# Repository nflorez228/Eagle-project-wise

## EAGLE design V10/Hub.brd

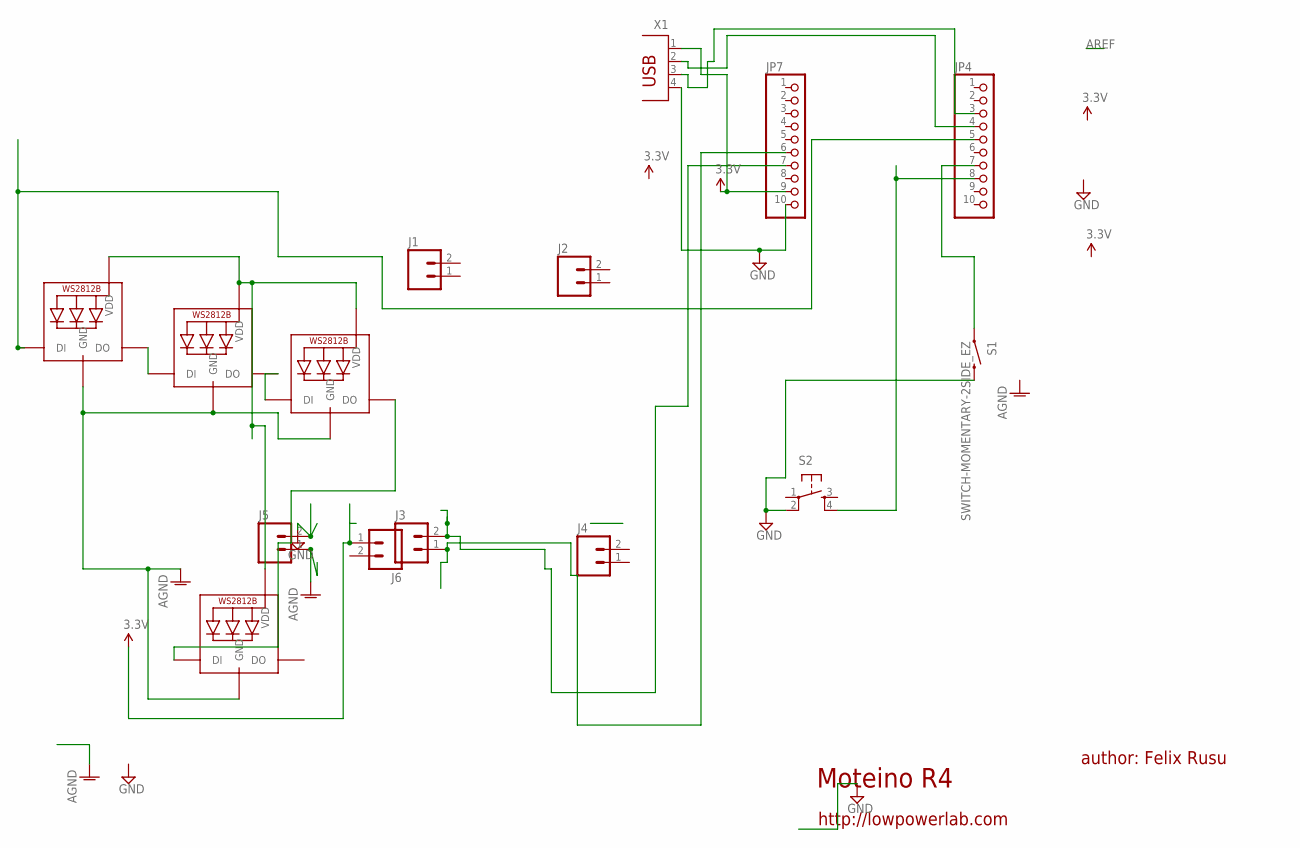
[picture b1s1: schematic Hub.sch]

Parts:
J1, J2, J3, J4, J5, J6: M02PTH; 1X02
JP4, JP7: PINHD-1X10; 1X10
LED1, LED2, LED3, LED5: WS2812B5050; WS2812B
S1: SWITCH-MOMENTARY-2SIDE_EZ; TACTILE-PTH-SIDEEZ
S2: TAC_SWITCHPTH; TACTILE-PTH
X1: PN87520

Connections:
AGND: J5.1, LED1.3-GND (GND), LED2.3-GND (GND), LED3.3-GND (GND), LED5.3-GND (GND)
GND: J5.2, JP7.10, S1.2, S2.2, X1.4
unnamed: JP4.8, S2.4
unnamed: LED3.2-DOUT (DO), LED5.4-DIN (DI)
unnamed: JP4.5, LED1.4-DIN (DI)
unnamed: LED1.1-VDD (VDD), LED2.1-VDD (VDD), LED3.1-VDD (VDD), LED5.1-VDD (VDD)
unnamed: JP4.7, S1.1
unnamed: J3.2, JP7.7
unnamed: J3.1, JP7.6
unnamed: JP4.4, X1.2
unnamed: JP4.3, X1.3
unnamed: LED2.2-DOUT (DO), LED3.4-DIN (DI)
unnamed: LED1.2-DOUT (DO), LED2.4-DIN (DI)
VCC: J6.1, JP7.9, X1.1

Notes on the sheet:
Moteino R4
author: Felix Rusu
http://lowpowerlab.com

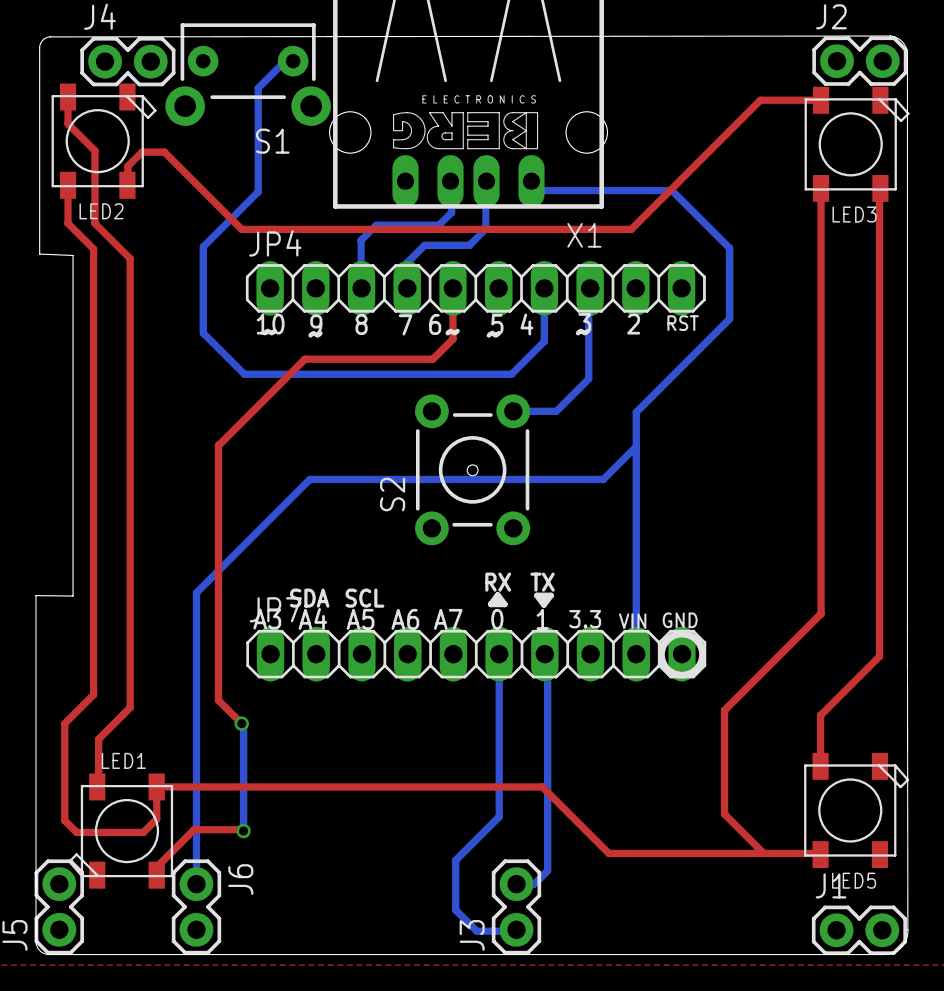
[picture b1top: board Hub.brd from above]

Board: 2 copper layers, 48.4 x 51.0 mm, 15 parts (0 on the bottom side), 14 nets.

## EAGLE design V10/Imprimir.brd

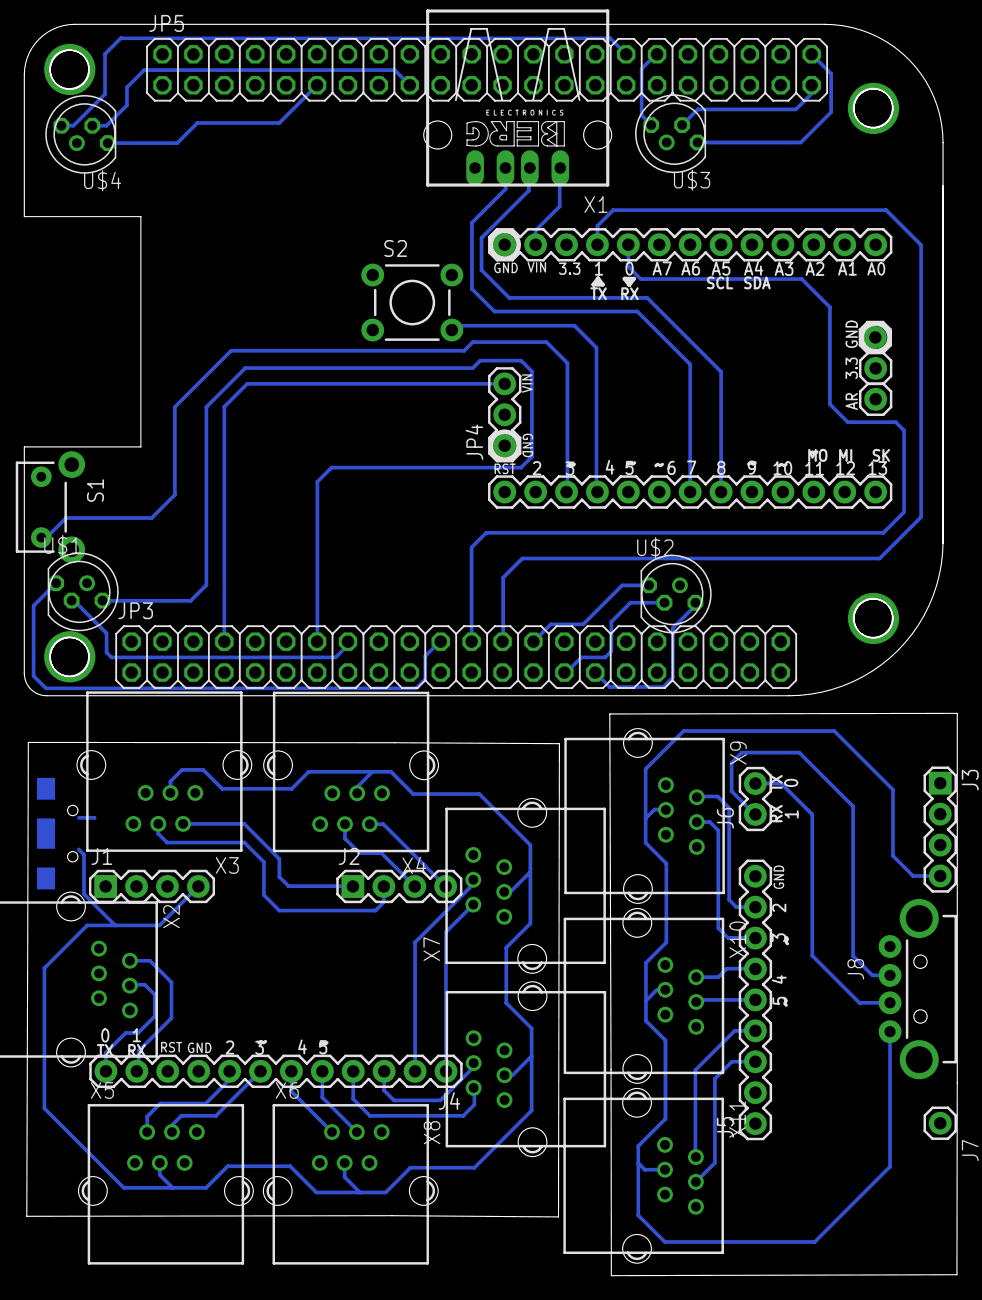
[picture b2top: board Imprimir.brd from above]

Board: 2 copper layers, 76.7 x 102.8 mm, 34 parts (1 on the bottom side), 47 nets.

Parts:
+: M01PTH; 1X01
ANALOGSIDE: M13; 1X13
DIGITALSIDE: M13; 1X13
J1, J2, J3: 1X04
J4: 1X12
J5: 1X09
J6: 1X02
J7: 1X01
J8: USB-A-H
JP1, JP2: M01PTH; 1X01
JP3, JP5: 2X22
JP4: 1X03
JP9: Micro USB; USB-AB-MICRO-SMD_V03
S1: SWITCH-MOMENTARY-2SIDE_EZ; TACTILE-PTH-SIDEEZ
S2: TACTILE-PTH
U$1, U$2, U$3, U$4: 5MMRGBLED; LED5MMRGB
X1: PN87520
X2, X3, X4, X5, X6, X7, X8, X9, X10, X11: YH-55-10

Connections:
GND: ANALOGSIDE.13, JP3.43, JP3.44, S1.1, S2.2, U$1.P$3, U$2.P$3, U$3.P$3, U$4.P$3, X1.4
GND1: J1.2, J4.9, JP9.GND1, X2.5, X3.5, X4.5, X5.5, X6.5, X7.5, X8.5
GND2: J3.2, J5.9, J8.VBUS, X9.5, X10.5, X11.5
unnamed: DIGITALSIDE.10, S2.4
unnamed: ANALOGSIDE.9, JP3.24
unnamed: JP3.14, U$1.P$4
unnamed: J4.12, X2.4
unnamed: JP3.16, U$1.P$2
unnamed: DIGITALSIDE.11, S1.2
unnamed: JP3.22, U$1.P$1
unnamed: JP3.28, U$2.P$1
unnamed: JP3.29, U$2.P$2
unnamed: JP3.31, U$2.P$4
unnamed: JP5.11, U$4.P$1
unnamed: JP5.17, U$4.P$2
unnamed: JP5.32, U$4.P$4
unnamed: JP5.43, U$3.P$2
unnamed: JP5.44, U$3.P$1
unnamed: JP5.34, U$3.P$4
unnamed: ANALOGSIDE.10, JP3.26
unnamed: DIGITALSIDE.7, X1.3
unnamed: ANALOGSIDE.12, X1.1
unnamed: DIGITALSIDE.6, X1.2
unnamed: J4.11, X2.2
unnamed: J4.7, X5.4
unnamed: J4.8, X5.2
unnamed: J4.5, X6.4
unnamed: J4.6, X6.2
unnamed: J4.3, X8.4
unnamed: J4.4, X8.2
unnamed: J4.2, X7.4
unnamed: J4.1, X7.2
unnamed: J2.4, X4.2
unnamed: J2.3, X4.4
unnamed: J2.2, X3.4
unnamed: J2.1, X3.2
unnamed: J5.7, X9.4
unnamed: J5.8, X9.2
unnamed: J5.5, X10.4
unnamed: J5.6, X10.2
unnamed: J5.3, X11.4
unnamed: J5.4, X11.2
unnamed: J6.2, J8.D+
unnamed: J6.1, J8.D-
VCC: JP3.8, JP4.3
VIN: J1.4, JP9.VBUS1, X3.3, X4.3, X5.3, X6.3, X7.3, X8.3
VIN1: J3.4, J8.GND, X9.3, X10.3, X11.3

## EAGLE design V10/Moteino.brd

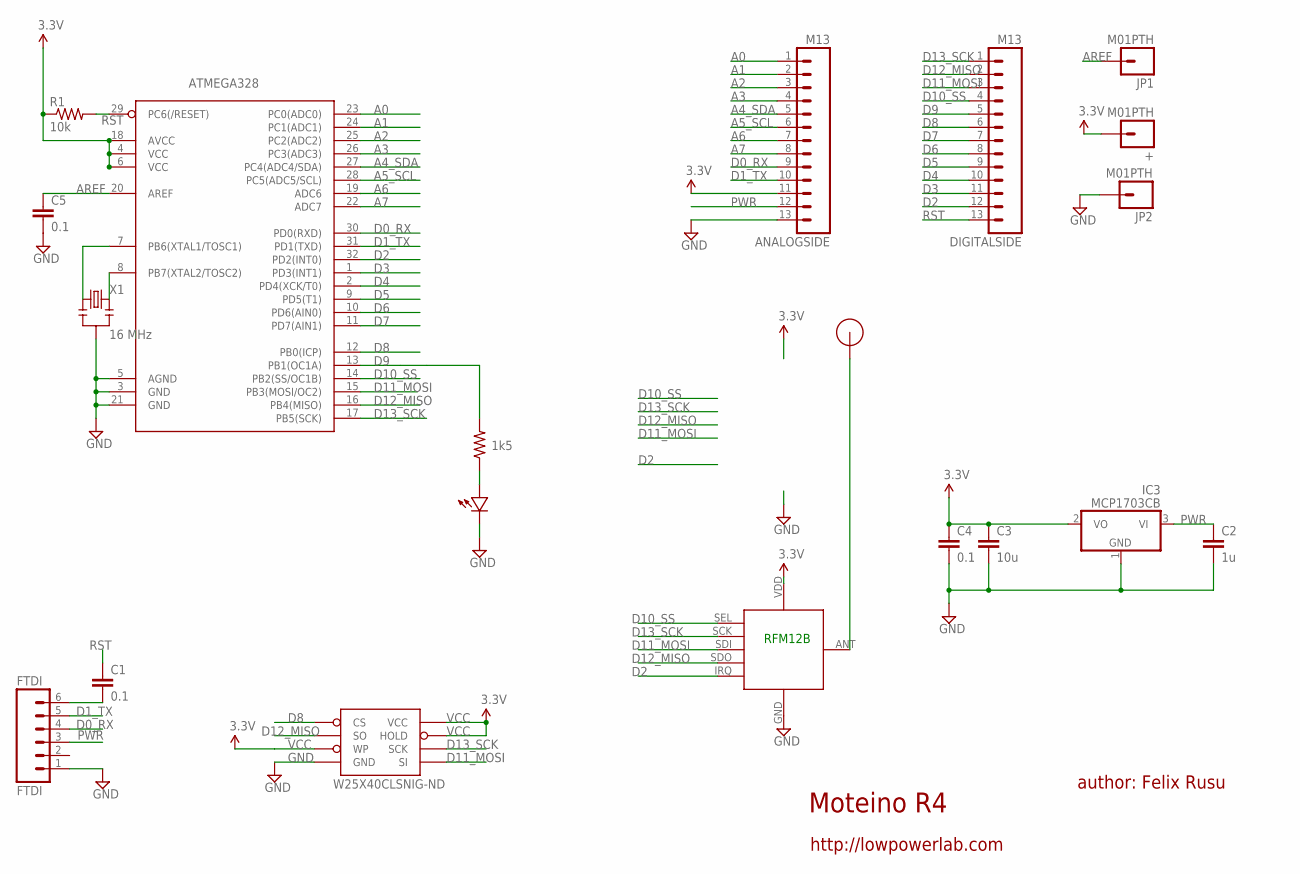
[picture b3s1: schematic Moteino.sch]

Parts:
+: M01PTH; 1X01
ANALOGSIDE: M13; 1X13
ATMEGA328: ATMega-328; TQFP32-08
C1, C4, C5: 0.1; 0603-CAP
C2: 1u; 0603-CAP
C3: 10u; 0805-CAP
DIGITALSIDE: M13; 1X13
FTDI: FTDI; 1X06
IC3: MCP1703CB; SOT23
JP1, JP2: M01PTH; 1X01
R1: 10k; 0603-RES
R2: 1k5; 0603-RES
RFM12B: RFM12B_MINPADS; RFM12B-MINPADS
U$1: RFM12B_ANTENNA; RFM12B-ANTENNA
U$2: LED0603; 0603-LED
W25X40CLSNIG-ND: AT25F512BWIDE_5.3MM; SO08WIDE
X1: 16 MHz; RESONATOR-SMD

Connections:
A0: ANALOGSIDE.1, ATMEGA328.23 (PC0(ADC0))
A1: ANALOGSIDE.2, ATMEGA328.24 (PC1(ADC1))
A2: ANALOGSIDE.3, ATMEGA328.25 (PC2(ADC2))
A3: ANALOGSIDE.4, ATMEGA328.26 (PC3(ADC3))
A4_SDA: ANALOGSIDE.5, ATMEGA328.27 (PC4(ADC4/SDA))
A5_SCL: ANALOGSIDE.6, ATMEGA328.28 (PC5(ADC5/SCL))
A6: ANALOGSIDE.7, ATMEGA328.19 (ADC6)
A7: ANALOGSIDE.8, ATMEGA328.22 (ADC7)
AREF: ATMEGA328.20 (AREF), C5.1, JP1.1
D0_RX: ANALOGSIDE.9, ATMEGA328.30 (PD0(RXD)), FTDI.4
D1_TX: ANALOGSIDE.10, ATMEGA328.31 (PD1(TXD)), FTDI.5
D2: ATMEGA328.32 (PD2(INT0)), DIGITALSIDE.12, RFM12B.IRQ
D3: ATMEGA328.1 (PD3(INT1)), DIGITALSIDE.11
D4: ATMEGA328.2 (PD4(XCK/T0)), DIGITALSIDE.10
D5: ATMEGA328.9 (PD5(T1)), DIGITALSIDE.9
D6: ATMEGA328.10 (PD6(AIN0)), DIGITALSIDE.8
D7: ATMEGA328.11 (PD7(AIN1)), DIGITALSIDE.7
D8: ATMEGA328.12 (PB0(ICP)), DIGITALSIDE.6, W25X40CLSNIG-ND.1 (CS)
D9: ATMEGA328.13 (PB1(OC1A)), DIGITALSIDE.5, R2.2
D10_SS: ATMEGA328.14 (PB2(SS/OC1B)), DIGITALSIDE.4, RFM12B.SEL
D11_MOSI: ATMEGA328.15 (PB3(MOSI/OC2)), DIGITALSIDE.3, RFM12B.SDI (SDI/MOSI), W25X40CLSNIG-ND.5 (SI)
D12_MISO: ATMEGA328.16 (PB4(MISO)), DIGITALSIDE.2, RFM12B.SDO (SDO/MISO), W25X40CLSNIG-ND.2 (SO)
D13_SCK: ATMEGA328.17 (PB5(SCK)), DIGITALSIDE.1, RFM12B.SCK, W25X40CLSNIG-ND.6 (SCK)
GND: ANALOGSIDE.13, ATMEGA328.3 (GND), ATMEGA328.5 (AGND), ATMEGA328.21 (GND), C2.2, C3.2, C4.2, C5.2, FTDI.1, IC3.1 (GND), JP2.1, RFM12B.GND, U$2.MINUS, W25X40CLSNIG-ND.4 (GND), X1.2
unnamed: ATMEGA328.7 (PB6(XTAL1/TOSC1)), X1.1
unnamed: R2.1, U$2.PLUS
unnamed: RFM12B.ANT, U$1.P$1
unnamed: C1.2, FTDI.6
unnamed: ATMEGA328.8 (PB7(XTAL2/TOSC2)), X1.3
PWR: ANALOGSIDE.12, C2.1, FTDI.3, IC3.3 (VI)
RST: ATMEGA328.29 (PC6(/RESET)), C1.1, DIGITALSIDE.13, R1.2
VCC: +.1, ANALOGSIDE.11, ATMEGA328.4 (VCC), ATMEGA328.6 (VCC), ATMEGA328.18 (AVCC), C3.1, C4.1, IC3.2 (VO), R1.1, RFM12B.VDD, W25X40CLSNIG-ND.3 (WP), W25X40CLSNIG-ND.7 (HOLD), W25X40CLSNIG-ND.8 (VCC)

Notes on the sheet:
Moteino R4
author: Felix Rusu
http://lowpowerlab.com
RFM12B

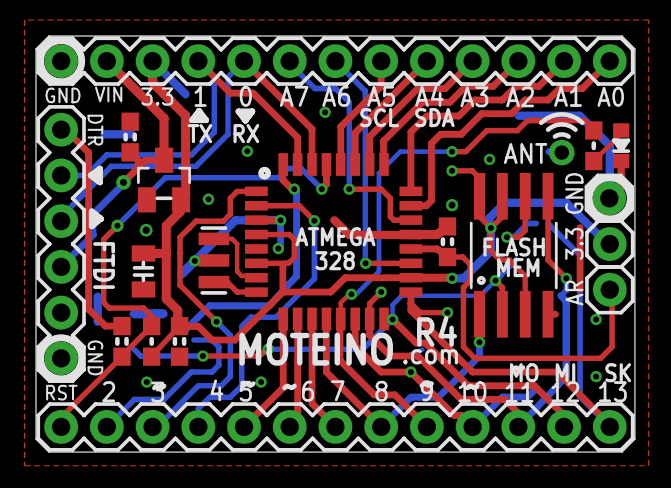
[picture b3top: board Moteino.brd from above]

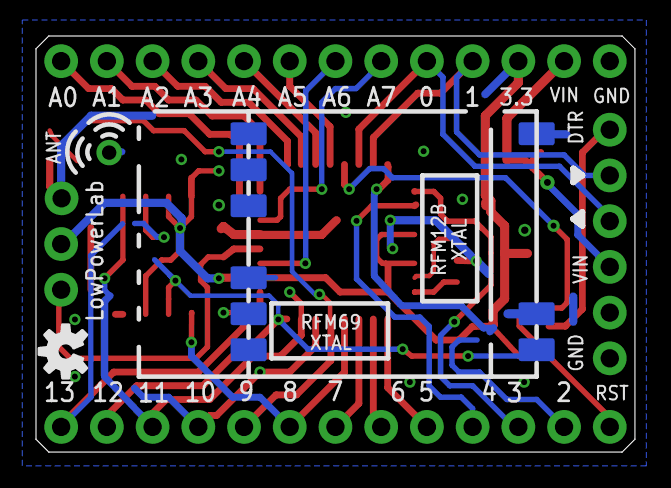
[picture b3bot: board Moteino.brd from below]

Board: 2 copper layers, 33.3 x 23.1 mm, 21 parts (2 on the bottom side), 32 nets.

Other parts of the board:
U$3: OSHW-LOGO-S

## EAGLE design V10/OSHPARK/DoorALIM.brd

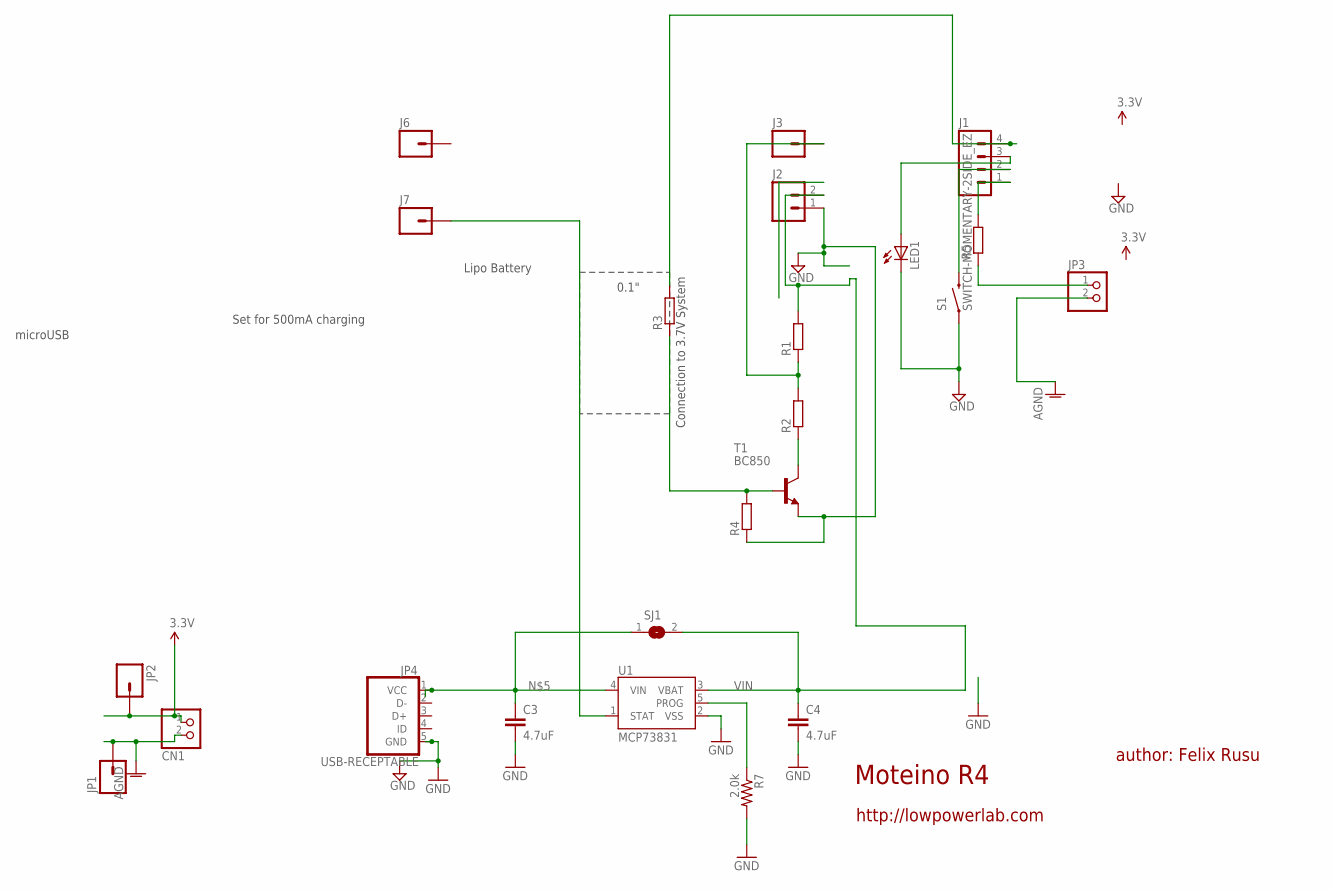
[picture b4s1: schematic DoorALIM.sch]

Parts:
C3, C4: 4.7uF; 0603-CAP
CN1: JST_2PIN-SMT; JST-PH-2-SMT
J1: M04PTH; 1X04
J2: M02PTH; 1X02
J3, J6, J7: M01PTH; 1X01
JP1, JP2: M01PTH; 1X01
JP3: PINHD-1X2; 1X02
JP4: USB-RECEPTABLE; FCI-10103594-0001LF
LED1: LED3MM
R1, R2, R5: R-EU_0204/7; 0204/7
R3, R4: R-EU_M1206; M1206
R7: 2.0k; 0603-RES
S1: SWITCH-MOMENTARY-2SIDE_EZ; TACTILE-PTH-SIDEEZ
SJ1: SJ
T1: BC850; SOT23
U1: MCP73831; SOT23-5

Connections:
AGND: CN1.2 (1), JP1.1, JP3.2
GND: C3.2, C4.2, J2.1, JP4.5 (GND), LED1.K (C), R4.1, R7.2, S1.1, T1.2 (E), U1.2 (VSS)
unnamed: J1.2, S1.2
unnamed: JP3.1, R5.1
unnamed: J1.3, LED1.A
unnamed: C3.1, JP4.1 (VCC), SJ1.1, U1.4 (VIN)
unnamed: J3.1, R1.1, R2.2
unnamed: R2.1, T1.3 (C)
unnamed: R3.1, R4.2, T1.1 (B)
unnamed: J1.4, R3.2
unnamed: J1.1, R5.2
unnamed: J7.1, U1.1 (STAT)
PROG: R7.1, U1.5 (PROG)
VCC: CN1.1 (2), JP2.1
VIN: C4.1, J2.2, R1.2, SJ1.2, U1.3 (VBAT)

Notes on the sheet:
Moteino R4
author: Felix Rusu
http://lowpowerlab.com
Set for 500mA charging
Connection to 3.7V System
0.1"
microUSB
Lipo Battery

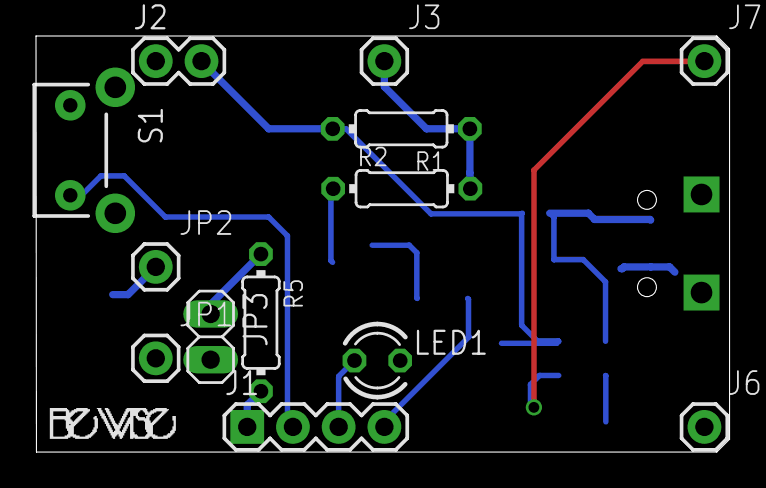
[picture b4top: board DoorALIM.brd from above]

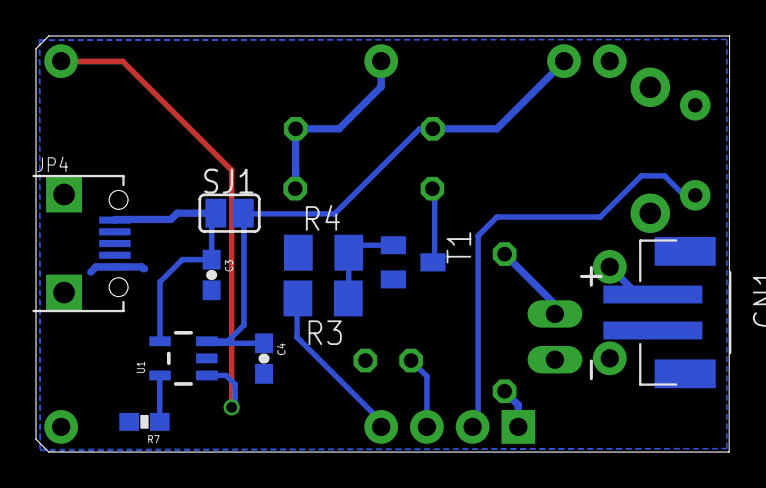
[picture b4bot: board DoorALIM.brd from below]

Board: 2 copper layers, 38.5 x 23.1 mm, 23 parts (10 on the bottom side), 15 nets.

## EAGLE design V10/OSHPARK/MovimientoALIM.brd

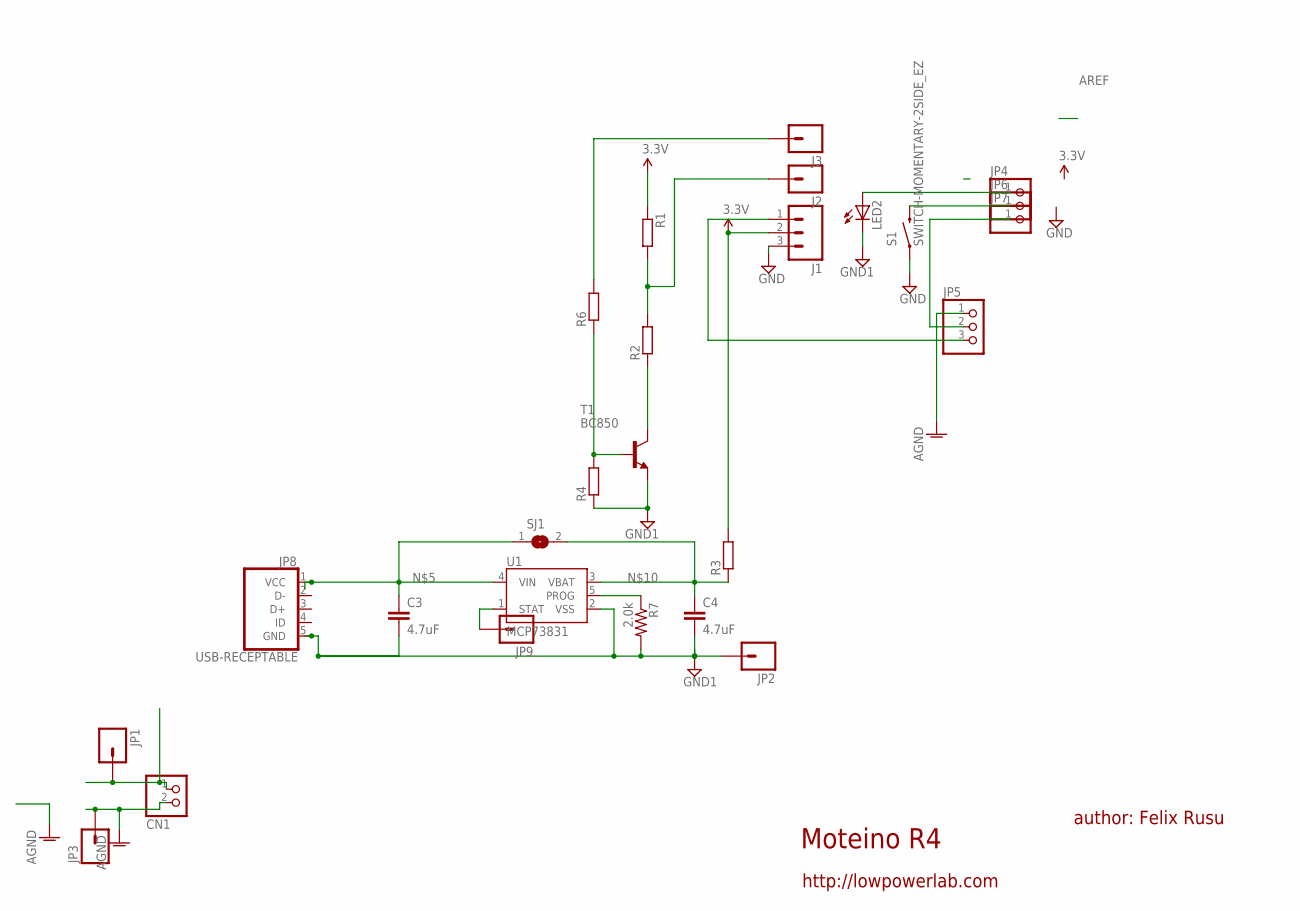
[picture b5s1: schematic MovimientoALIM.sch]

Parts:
C3, C4: 4.7uF; 0603-CAP
CN1: JST_2PIN-SMT; JST-PH-2-SMT
J1: M03PTH; 1X03
J2, J3: M01PTH; 1X01
JP1, JP2, JP3, JP9: M01PTH; 1X01
JP4, JP6, JP7: PINHD-1X1; 1X01
JP5: PINHD-1X3; 1X03
JP8: USB-RECEPTABLE; FCI-10103594-0001LF
LED2: LED3MM
R1, R2: R-EU_0204/7; 0204/7
R3, R4, R6: R-EU_M1206; M1206
R7: 2.0k; 0603-RES
S1: SWITCH-MOMENTARY-2SIDE_EZ; TACTILE-PTH-SIDEEZ
SJ1: SJ
T1: BC850; SOT23
U1: MCP73831; SOT23-5

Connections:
AGND: CN1.2 (1), JP3.1, JP5.1
GND: J1.3, S1.1
GND1: C3.2, C4.2, JP2.1, JP8.5 (GND), LED2.K (C), R4.1, R7.2, T1.2 (E), U1.2 (VSS)
unnamed: JP6.1, S1.2
unnamed: JP5.2, JP7.1
unnamed: J3.1, R6.2
unnamed: C3.1, JP8.1 (VCC), SJ1.1, U1.4 (VIN)
unnamed: J2.1, R1.2, R2.2
unnamed: R2.1, T1.3 (C)
unnamed: R4.2, R6.1, T1.1 (B)
unnamed: J1.1, JP5.3
unnamed: C4.1, R3.1, SJ1.2, U1.3 (VBAT)
unnamed: JP4.1, LED2.A
unnamed: CN1.1 (2), JP1.1
unnamed: JP9.1, U1.1 (STAT)
PROG: R7.1, U1.5 (PROG)
VCC: J1.2, R1.1, R3.2

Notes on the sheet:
Moteino R4
author: Felix Rusu
http://lowpowerlab.com

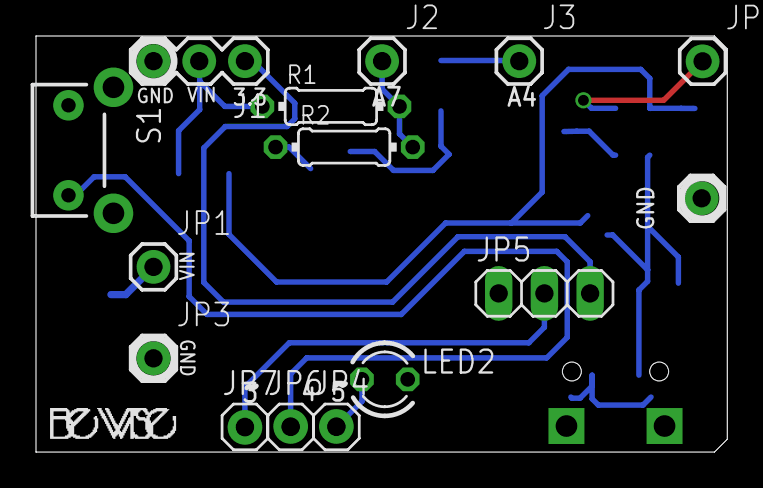
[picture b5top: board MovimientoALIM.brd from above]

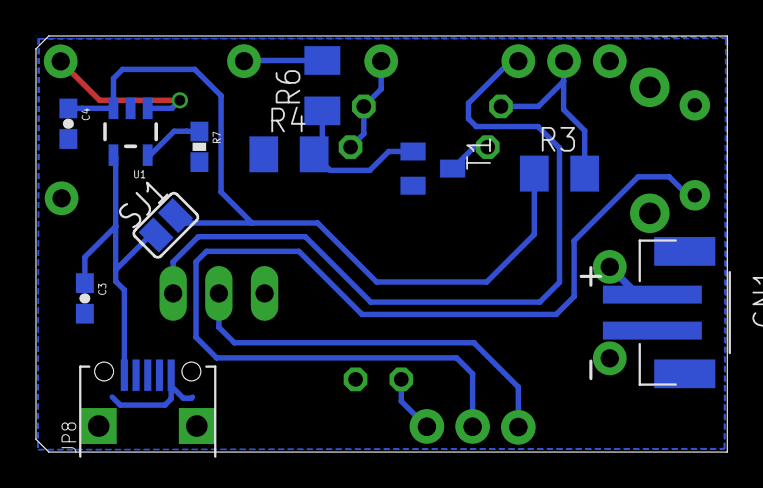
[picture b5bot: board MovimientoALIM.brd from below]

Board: 2 copper layers, 38.4 x 23.1 mm, 26 parts (11 on the bottom side), 17 nets.

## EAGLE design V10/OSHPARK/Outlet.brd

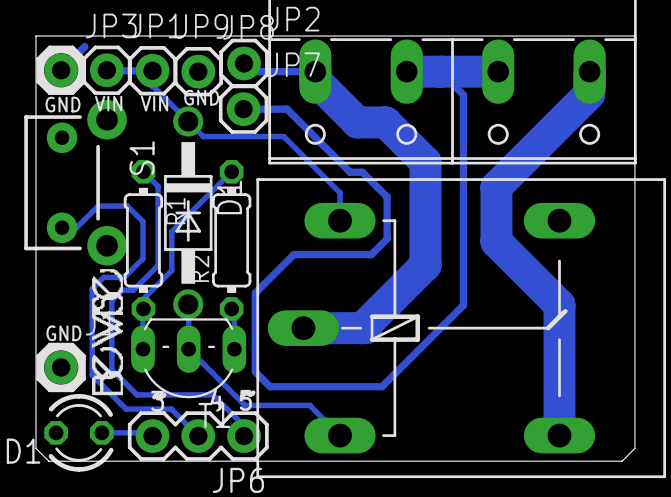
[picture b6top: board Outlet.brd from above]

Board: 2 copper layers, 33.3 x 23.6 mm, 16 parts (0 on the bottom side), 11 nets.

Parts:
D1: 1N4004; DO41-10
J1: 1X01
JP1, JP2, JP3, JP7, JP8, JP9: 1X01
JP6: 1X03
K1: G5L; G5LE
LED1: LED3MM
R1, R2: 0204/7
S1: SWITCH-MOMENTARY-2SIDE_EZ; TACTILE-PTH-SIDEEZ
T1: 2SC458; TO92-ECB
X1: Out- In- Out+ In+; W237-4P

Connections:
AGND: J1.1, LED1.K
GND: JP3.1, JP8.1, R2.1, S1.1, T1.E
unnamed: JP6.2, S1.2
unnamed: JP7.1, X1.2, X1.3
unnamed: JP6.3, LED1.A
unnamed: R1.2, R2.2, T1.B
unnamed: D1.A, K1.1, T1.C
unnamed: D1.C, JP1.1, JP9.1, K1.2
unnamed: K1.S, X1.1
unnamed: JP2.1, K1.P, X1.4
unnamed: JP6.1, R1.1

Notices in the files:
parts and their libraries:
SparkFun-Connectors: Licensing: CC v3.0 Share-Alike You are welcome to use this library for commercial purposes.
SparkFun-Retired: Licensing:Creative Commons ShareAlike 4.0 International - https://creativecommons.org/licenses/by-sa/4.0
